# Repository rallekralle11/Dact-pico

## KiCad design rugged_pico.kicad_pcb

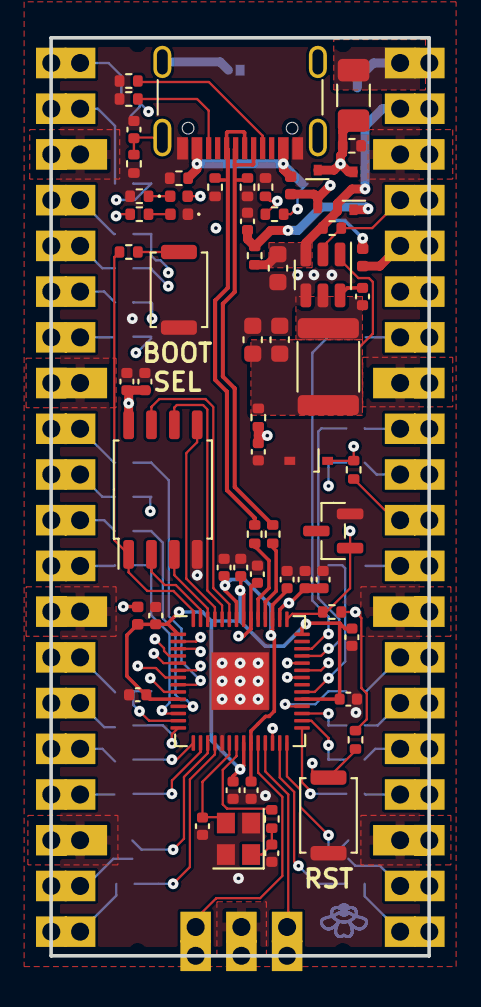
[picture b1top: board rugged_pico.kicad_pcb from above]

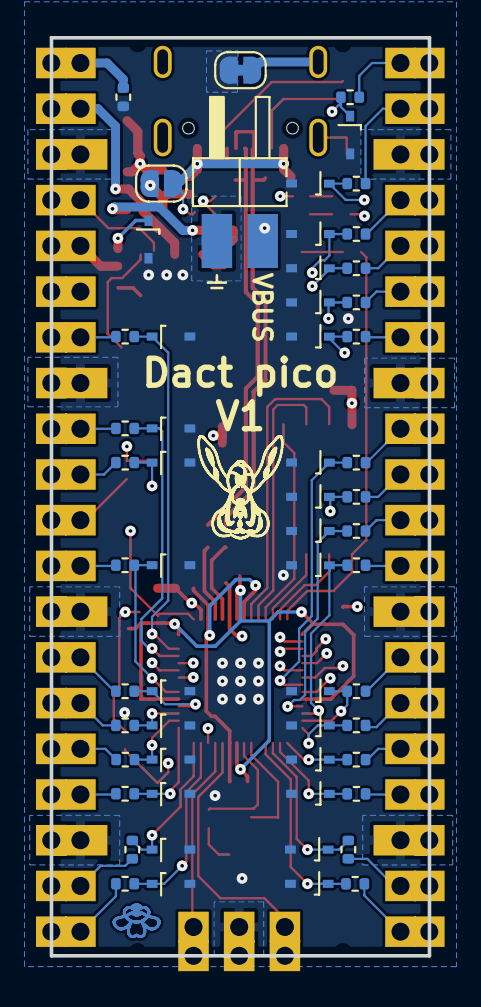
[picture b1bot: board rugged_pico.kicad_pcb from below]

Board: 4 copper layers, 21.0 x 51.0 mm, 125 parts (57 on the bottom side), 93 nets.

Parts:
C1, C2: 20pf; C_0402_1005Metric
C3, C4, C7, C10, C12, C13, C14, C15, C16, C17, C18, C21: 100nf; C_0402_1005Metric
C5, C11, C19, C22: 2,2µf; C_0402_1005Metric
C6: 10µf; C_0603_1608Metric
C8, C9: 22µf; C_0603_1608Metric
C20, C23: 100nF; C_0402_1005Metric
D1, D5, D6, D7, D8, D9, D10, D11, D12, D13, D14, D15, D16, D17, D18, D19, D20, D21, D22, D23, D24, D27, D28, D29, D30, D31, D32, D33: Zener_3,5V; SOD323_zener
D2, D26: D_Small; SOD323_vanlig
D3: LED_GREEN; LED_0402_1005Metric
D4: LED_GREEN_PWR; LED_0402_1005Metric
F1: 750mA; Fuse_0402_1005Metric
F2: 500mA; Fuse_0402_1005Metric
F23: 50mA; Fuse_0402_1005Metric
F25: 750mA; Fuse_1206_3216Metric
FB1, FB2: FerriteBead_Small; R_0402_1005Metric
J1, J2, J5, J6: Conn_01x20; PinSocket_1x20_P2.54mm_Vertical
J3: USB_C_Receptacle_USB2.0; USB_C_Receptacle_G-Switch_GT-USB-7010ASV
J4, J7: Debug; PinSocket_1x03_P2.54mm_Vertical
J8: Screw_Terminal_01x02; PinHeader_1x02_P2.54mm_Horizontal
JP1: Jumper; SolderJumper-2_P1.3mm_Open_RoundedPad1.0x1.5mm
JP2: Jumper; SolderJumper-2_P1.3mm_Bridged_RoundedPad1.0x1.5mm
L1: 3,9µH; L_1812_4532Metric
R1, R2: 27Ω; R_0402_1005Metric
R3, R11, R12, R14: 1kΩ; R_0402_1005Metric
R4: 5,6kΩ; R_0402_1005Metric
R5, R19: 10kΩ; R_0402_1005Metric
R6, R15: 100kΩ; R_0402_1005Metric
R7, R8: 5,1kΩ; R_0402_1005Metric
R9, R10: 470Ω; R_0402_1005Metric
R13, R16, R17, R18, R46: Var_Small; R_0402_1005Metric
R20, R21, R22, R23, R24, R25, R26, R27, R28, R29, R30, R31, R32, R33, R34, R35, R36, R37, R38, R39, R40, R41, R42, R43, R44, R45: 220Ω; R_0402_1005Metric
SW1, SW2: SW_Push; SW_Push_SPST_NO_Alps_SKRK
U1: RP2040; QFN-56-1EP_7x7mm_P0.4mm_EP3.2x3.2mm
U2: AP63203WU; TSOT-23-6
U3: W25Q16JVSSIQ; SOIC-8_5.23x5.23mm_P1.27mm
U4: LM4040DBZ-3; SOT-23_bättre (2022_12_20 17_46_41 UTC)
Y1: Crystal_GND24_Small; Crystal_SMD_2520-4Pin_2.5x2.0mm

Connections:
3,3V_EN: J1.4, J5.4, R6.2, U2.2 (EN)
+1V1: C3.2, C4.2, C5.2, U1.23 (DVDD), U1.45 (VREG_VOUT), U1.50 (DVDD)
+3.3V: C10.1, C11.1, C15.1, C18.1, C19.1, C22.1, D27.1 (K), F1.1, F23.2, FB2.2, R9.1, R14.1, R15.2, U1.44 (VREG_IN), U1.48 (USB_VDD), U3.8 (VCC)
/BUCK: C7.2, L1.1, U2.5 (SW)
/BUCK_U: C8.1, C9.1, FB2.1, L1.2, U2.1 (FB)
/BUSIN: F25.2, J1.1, J5.1, R13.2
AREF: J1.6, J5.6, R14.2, U1.43 (ADC_AVDD), U4.1 (K)
D+: J3.A6 (D+), J3.B6 (D+), R1.2, R16.2
D-: J3.A7 (D-), J3.B7 (D-), R2.1, R17.2
DN: R2.2, U1.46 (USB_DM)
DP: R1.1, U1.47 (USB_DP)
GND: C1.1, C2.1, C3.1, C4.1, C5.1, C6.2, C8.2, C9.2, C10.2, C11.2, C12.2, C13.2, C14.2, C15.2, C16.2, C17.1, C18.2, C19.2, C20.2, C21.2, C22.2, C23.2, D1.2 (A), D4.1 (K), D5.2 (A), D6.2 (A), D7.2 (A), D8.2 (A), D9.2 (A), D10.2 (A), D11.2 (A), D12.2 (A), D13.2 (A), D14.2 (A), D15.2 (A), D16.2 (A), D17.2 (A), D18.2 (A), D19.2 (A), D20.2 (A), D21.2 (A), D22.2 (A), D23.2 (A), D24.2 (A), D27.2 (A), D28.2 (A), D29.2 (A), D30.2 (A), D31.2 (A), D32.2 (A), D33.2 (A), J1.3, J1.8, J1.13, J1.18, J2.3, J2.8, J2.13, J2.18, J3.A1 (GND), J3.A12 (GND), J3.B1 (GND), J3.B12 (GND), J4.2, J5.3, J5.8, J5.13, J5.18, J6.3, J6.8, J6.13, J6.18, J7.2, J8.1, JP2.1 (A), R5.2, R7.2, R8.1, R10.2, R13.1, R16.1, R17.1, R18.1, R19.2, R46.1, SW1.1, SW2.1, U1.19 (TESTEN), U1.57 (GND), U2.4 (GND), U3.4 (GND), U4.2 (A), Y1.2, Y1.4
GPIO00: D1.1 (K), R30.1, U1.2 (GPIO0)
GPIO00-: J2.1, J6.1, R30.2
GPIO01: D5.1 (K), R29.1, U1.3 (GPIO1)
GPIO01-: J2.2, J6.2, R29.2
GPIO02: D6.1 (K), R28.1, U1.4 (GPIO2)
GPIO02-: J2.4, J6.4, R28.2
GPIO03: D7.1 (K), R27.1, U1.5 (GPIO3)
GPIO03-: J2.5, J6.5, R27.2
GPIO04: D8.1 (K), R26.1, U1.6 (GPIO4)
GPIO04-: J2.6, J6.6, R26.2
GPIO05: D9.1 (K), R25.1, U1.7 (GPIO5)
GPIO05-: J2.7, J6.7, R25.2
GPIO06: D10.1 (K), R24.1, U1.8 (GPIO6)
GPIO06-: J2.9, J6.9, R24.2
GPIO07: D11.1 (K), R23.1, U1.9 (GPIO7)
GPIO07-: J2.10, J6.10, R23.2
GPIO08: D12.1 (K), R22.1, U1.11 (GPIO8)
GPIO08-: J2.11, J6.11, R22.2
GPIO09: D13.1 (K), R21.1, U1.12 (GPIO9)
GPIO09-: J2.12, J6.12, R21.2
GPIO10: D14.1 (K), R31.1, U1.13 (GPIO10)
GPIO10-: J2.14, J6.14, R31.2
GPIO11: D15.1 (K), R32.1, U1.14 (GPIO11)
GPIO11-: J2.15, J6.15, R32.2
GPIO12: D16.1 (K), R33.1, U1.15 (GPIO12)
GPIO12-: J2.16, J6.16, R33.2
GPIO13: D30.1 (K), R34.1, U1.16 (GPIO13)
GPIO13-: J2.17, J6.17, R34.2
GPIO14: D31.1 (K), R35.1, U1.17 (GPIO14)
GPIO14-: J2.19, J6.19, R35.2
GPIO15: D17.1 (K), R36.1, U1.18 (GPIO15)
GPIO15-: J2.20, J6.20, R36.2
GPIO16: D18.1 (K), R37.1, U1.27 (GPIO16)
GPIO16-: J1.20, J5.20, R37.2
GPIO17: D19.1 (K), R38.1, U1.28 (GPIO17)
GPIO17-: J1.19, J5.19, R38.2
GPIO18: D20.1 (K), R39.1, U1.29 (GPIO18)
GPIO18-: J1.17, J5.17, R39.2
GPIO19: D21.1 (K), R20.1, U1.30 (GPIO19)
GPIO19-: J1.16, J5.16, R20.2
GPIO20: D22.1 (K), R45.1, U1.31 (GPIO20)
GPIO20-: J1.15, J5.15, R45.2
GPIO21: D23.1 (K), R44.1, U1.32 (GPIO21)
GPIO21-: J1.14, J5.14, R44.2
GPIO22: D24.1 (K), R43.1, U1.34 (GPIO22)
GPIO22-: J1.12, J5.12, R43.2
GPIO24: R4.2, R5.1, U1.36 (GPIO24)
GPIO25: D3.2 (A), U1.37 (GPIO25)
GPIO26: D28.1 (K), R42.1, U1.38 (GPIO26_ADC0)
GPIO26-: J1.10, J5.10, R42.2
GPIO27: D29.1 (K), R41.1, U1.39 (GPIO27_ADC1)
GPIO27-: J1.9, J5.9, R41.2
GPIO28: D32.1 (K), R40.1, U1.40 (GPIO28_ADC2)
GPIO28-: J1.7, J5.7, R40.2
unnamed: C2.2, R3.2, Y1.1
unnamed: C12.1, C13.1, C14.1, C16.1, C17.2, C21.1, F23.1, U1.1 (IOVDD), U1.10 (IOVDD), U1.22 (IOVDD), U1.33 (IOVDD), U1.42 (IOVDD), U1.49 (IOVDD)
unnamed: C23.1, D2.1 (K), FB1.1
unnamed: D3.1 (K), R10.1
unnamed: D4.2 (A), R9.2
unnamed: D26.2 (A), F2.2, JP1.1 (A)
unnamed: D33.1 (K), R12.1, U1.26 (RUN)
unnamed: F1.2, J1.5, J5.5
unnamed: J3.A5 (CC1), R8.2
unnamed: J3.B5 (CC2), R7.1
unnamed: C20.1, J3.S1 (SHIELD), JP2.2 (B), R19.1
unnamed: F2.1, J3.A4 (VBUS), J3.A9 (VBUS), J3.B4 (VBUS), J3.B9 (VBUS), JP1.2 (B), R4.1, R46.2
unnamed: R11.1, SW1.2
unnamed: C1.2, U1.20 (XIN), Y1.3
unnamed: R3.1, U1.21 (XOUT)
unnamed: C7.1, U2.6 (BST)
QSPI_SCLK: U1.52 (QSPI_SCLK), U3.6 (CLK)
QSPI_SD0: U1.53 (QSPI_SD0), U3.5 (DI(IO0))
QSPI_SD1: U1.55 (QSPI_SD1), U3.2 (DO(IO1))
QSPI_SD2: U1.54 (QSPI_SD2), U3.3 (IO2)
QSPI_SD3: U1.51 (QSPI_SD3), U3.7 (IO3)
QSPI_SS: R11.2, U1.56 (QSPI_SS), U3.1 (~CS)
RST: J1.11, J5.11, R12.2, R15.1, SW2.2
SWCLK: J4.1, J7.1, U1.24 (SWCLK)
SWD: J4.3, J7.3, U1.25 (SWD)
VBUS: D2.2 (A), D26.1 (K), F25.1, J8.2, R18.2
VSYS: C6.1, FB1.2, J1.2, J5.2, R6.1, U2.3 (IN)

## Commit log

2024-02-04 init
2024-02-04 pictures
